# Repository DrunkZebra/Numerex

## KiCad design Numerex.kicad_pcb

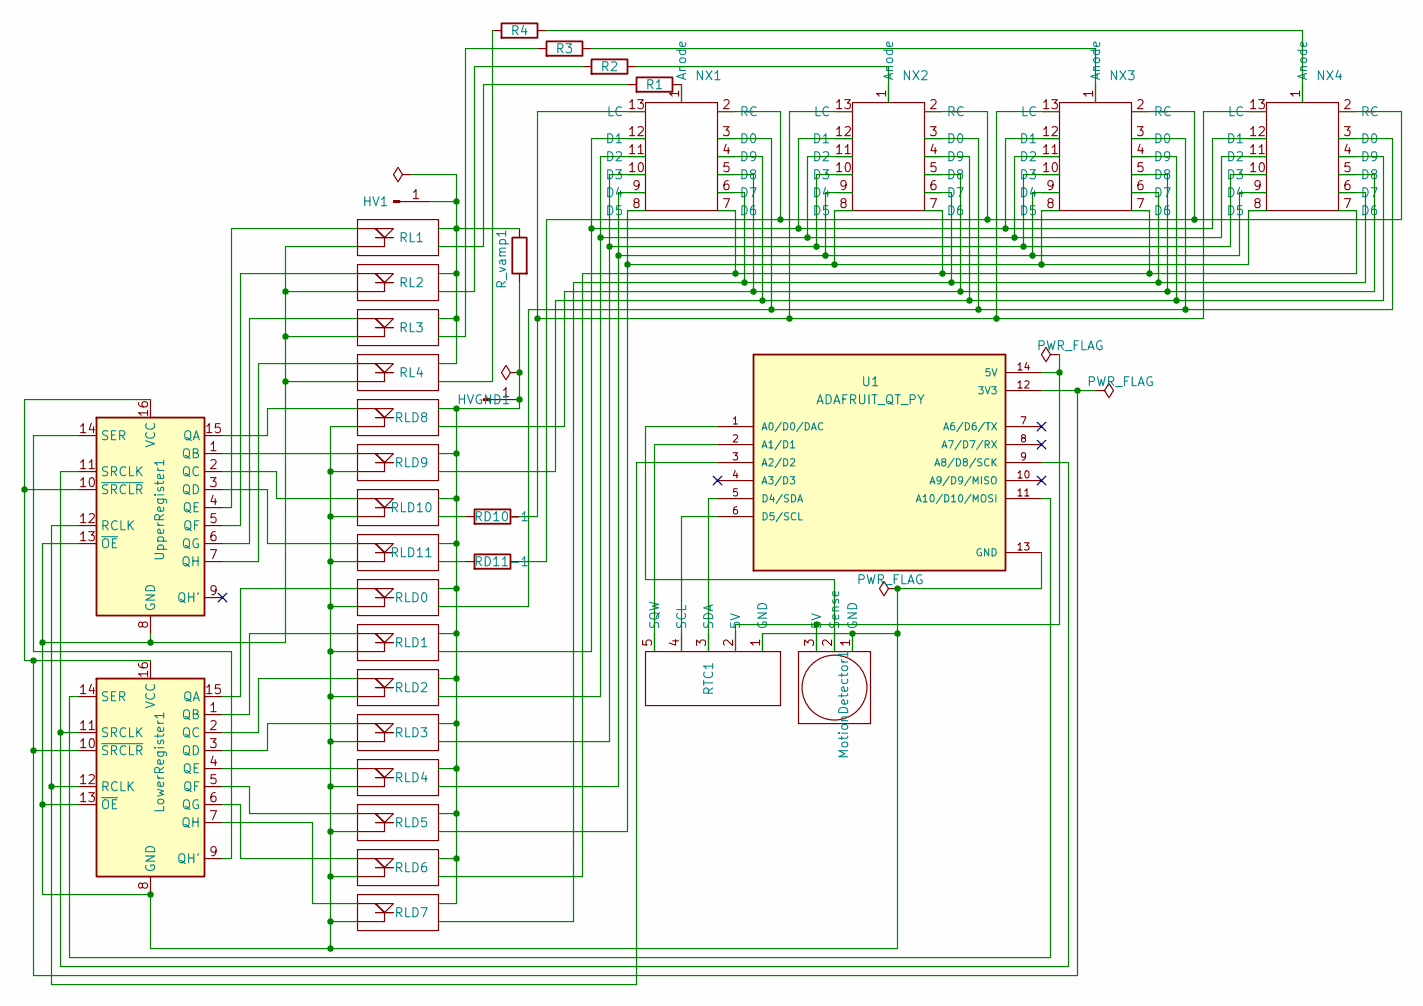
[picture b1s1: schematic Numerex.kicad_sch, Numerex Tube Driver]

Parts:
HV1: 170; PinHeader_1x01_P1.00mm_Vertical
HVGND1: PinHeader_1x01_P1.00mm_Vertical
LowerRegister1: SN74HC595DR; SOIC-16_3.9x9.9mm_P1.27mm
MotionDetector1: PinHeader_1x03_P2.54mm_Vertical
NX1, NX2, NX3, NX4: IN-14
R1, R2, R3, R4: 22k; R_1206_3216Metric_Pad1.30x1.75mm_HandSolder
RD10-1, RD11-1: 10k; R_1206_3216Metric_Pad1.30x1.75mm_HandSolder
RL1, RL2, RL3, RL4: SOP-4_3.8x4.1mm_P2.54mm
RLD0, RLD1, RLD2, RLD3, RLD4, RLD5, RLD6, RLD7, RLD8, RLD9, RLD10, RLD11: SOP-4_3.8x4.1mm_P2.54mm
RTC1: RTC
R_vamp1: 22k; R_1206_3216Metric_Pad1.30x1.75mm_HandSolder
U1: ADAFRUIT_QT_PY; MODULE_ADAFRUIT_QT_PY; PARTREV 2022-12-12
UpperRegister1: SN74HC595DR; SOIC-16_3.9x9.9mm_P1.27mm

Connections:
unnamed 0: HV1.1, RL1.4 (VL), RL2.4 (VL), RL3.4 (VL), RL4.4 (VL), R_vamp1.2; also elsewhere on the board
unnamed 1: HVGND1.1, RLD0.4 (VL), RLD1.4 (VL), RLD2.4 (VL), RLD3.4 (VL), RLD4.4 (VL), RLD5.4 (VL), RLD6.4 (VL), RLD7.4 (VL), RLD8.4 (VL), RLD9.4 (VL), RLD10.4 (VL), RLD11.4 (VL), R_vamp1.1; also elsewhere on the board
unnamed 2: LowerRegister1.8 (GND), LowerRegister1.13 (~OE), MotionDetector1.1 (GND), RL1.2 (Diode-), RL2.2 (Diode-), RL3.2 (Diode-), RL4.2 (Diode-), RLD0.2 (Diode-), RLD1.2 (Diode-), RLD2.2 (Diode-), RLD3.2 (Diode-), RLD4.2 (Diode-), RLD5.2 (Diode-), RLD6.2 (Diode-), RLD7.2 (Diode-), RLD8.2 (Diode-), RLD9.2 (Diode-), RLD10.2 (Diode-), RLD11.2 (Diode-), RTC1.1 (GND), U1.13 (GND), UpperRegister1.8 (GND), UpperRegister1.13 (~OE); also elsewhere on the board
unnamed: LowerRegister1.15 (QA), RLD0.1 (Diode+)
unnamed: LowerRegister1.1 (QB), RLD1.1 (Diode+)
unnamed: LowerRegister1.2 (QC), RLD2.1 (Diode+)
unnamed: LowerRegister1.3 (QD), RLD3.1 (Diode+)
unnamed: LowerRegister1.4 (QE), RLD4.1 (Diode+)
unnamed: LowerRegister1.5 (QF), RLD5.1 (Diode+)
unnamed: LowerRegister1.6 (QG), RLD6.1 (Diode+)
unnamed: LowerRegister1.9 (QH'), UpperRegister1.14 (SER)
unnamed: LowerRegister1.7 (QH), RLD7.1 (Diode+)
unnamed 12: LowerRegister1.12 (RCLK), U1.3 (A2/D2), UpperRegister1.12 (RCLK); also elsewhere on the board
unnamed 13: LowerRegister1.14 (SER), U1.11 (A10/D10/MOSI); also elsewhere on the board
unnamed 14: LowerRegister1.11 (SRCLK), U1.9 (A8/D8/SCK), UpperRegister1.11 (SRCLK); also elsewhere on the board
unnamed 15: LowerRegister1.10 (~SRCLR), LowerRegister1.16 (VCC), U1.12 (3V3), UpperRegister1.10 (~SRCLR), UpperRegister1.16 (VCC); also elsewhere on the board
unnamed 16: MotionDetector1.3 (5V), RTC1.2 (5V), U1.14 (5V); also elsewhere on the board
unnamed 17: MotionDetector1.2 (Sense), U1.1 (A0/D0/DAC); also elsewhere on the board
unnamed: NX1.1 (Anode), R1.2
unnamed: NX1.3 (D0), NX2.3 (D0), NX3.3 (D0), NX4.3 (D0), RLD0.3 (Load)
unnamed: NX1.12 (D1), NX2.12 (D1), NX3.12 (D1), NX4.12 (D1), RLD1.3 (Load)
unnamed: NX1.11 (D2), NX2.11 (D2), NX3.11 (D2), NX4.11 (D2), RLD2.3 (Load)
unnamed: NX1.10 (D3), NX2.10 (D3), NX3.10 (D3), NX4.10 (D3), RLD3.3 (Load)
unnamed: NX1.9 (D4), NX2.9 (D4), NX3.9 (D4), NX4.9 (D4), RLD4.3 (Load)
unnamed: NX1.8 (D5), NX2.8 (D5), NX3.8 (D5), NX4.8 (D5), RLD5.3 (Load)
unnamed: NX1.7 (D6), NX2.7 (D6), NX3.7 (D6), NX4.7 (D6), RLD6.3 (Load)
unnamed: NX1.6 (D7), NX2.6 (D7), NX3.6 (D7), NX4.6 (D7), RLD7.3 (Load)
unnamed: NX1.5 (D8), NX2.5 (D8), NX3.5 (D8), NX4.5 (D8), RLD8.3 (Load)
unnamed: NX1.4 (D9), NX2.4 (D9), NX3.4 (D9), NX4.4 (D9), RLD9.3 (Load)
unnamed: NX1.13 (LC), NX2.13 (LC), NX3.13 (LC), NX4.13 (LC), RD10-1.2
unnamed: NX1.2 (RC), NX2.2 (RC), NX3.2 (RC), NX4.2 (RC), RD11-1.2
unnamed: NX2.1 (Anode), R2.2
unnamed: NX3.1 (Anode), R3.2
unnamed: NX4.1 (Anode), R4.2
unnamed: RL1.1 (Diode+), UpperRegister1.4 (QE)
unnamed: R1.1, RL1.3 (Load)
unnamed: RL2.1 (Diode+), UpperRegister1.5 (QF)
unnamed: R2.1, RL2.3 (Load)
unnamed: RL3.1 (Diode+), UpperRegister1.6 (QG)
unnamed: R3.1, RL3.3 (Load)
unnamed: RL4.1 (Diode+), UpperRegister1.7 (QH)
unnamed: R4.1, RL4.3 (Load)
unnamed: RLD8.1 (Diode+), UpperRegister1.15 (QA)
unnamed: RLD9.1 (Diode+), UpperRegister1.1 (QB)
unnamed: RLD10.1 (Diode+), UpperRegister1.2 (QC)
unnamed: RD10-1.1, RLD10.3 (Load)
unnamed: RLD11.1 (Diode+), UpperRegister1.3 (QD)
unnamed: RD11-1.1, RLD11.3 (Load)
unnamed 48: RTC1.4 (SCL), U1.6 (D5/SCL); also elsewhere on the board
unnamed 49: RTC1.3 (SDA), U1.5 (D4/SDA); also elsewhere on the board
unnamed 50: RTC1.5 (SQW), U1.2 (A1/D1); also elsewhere on the board

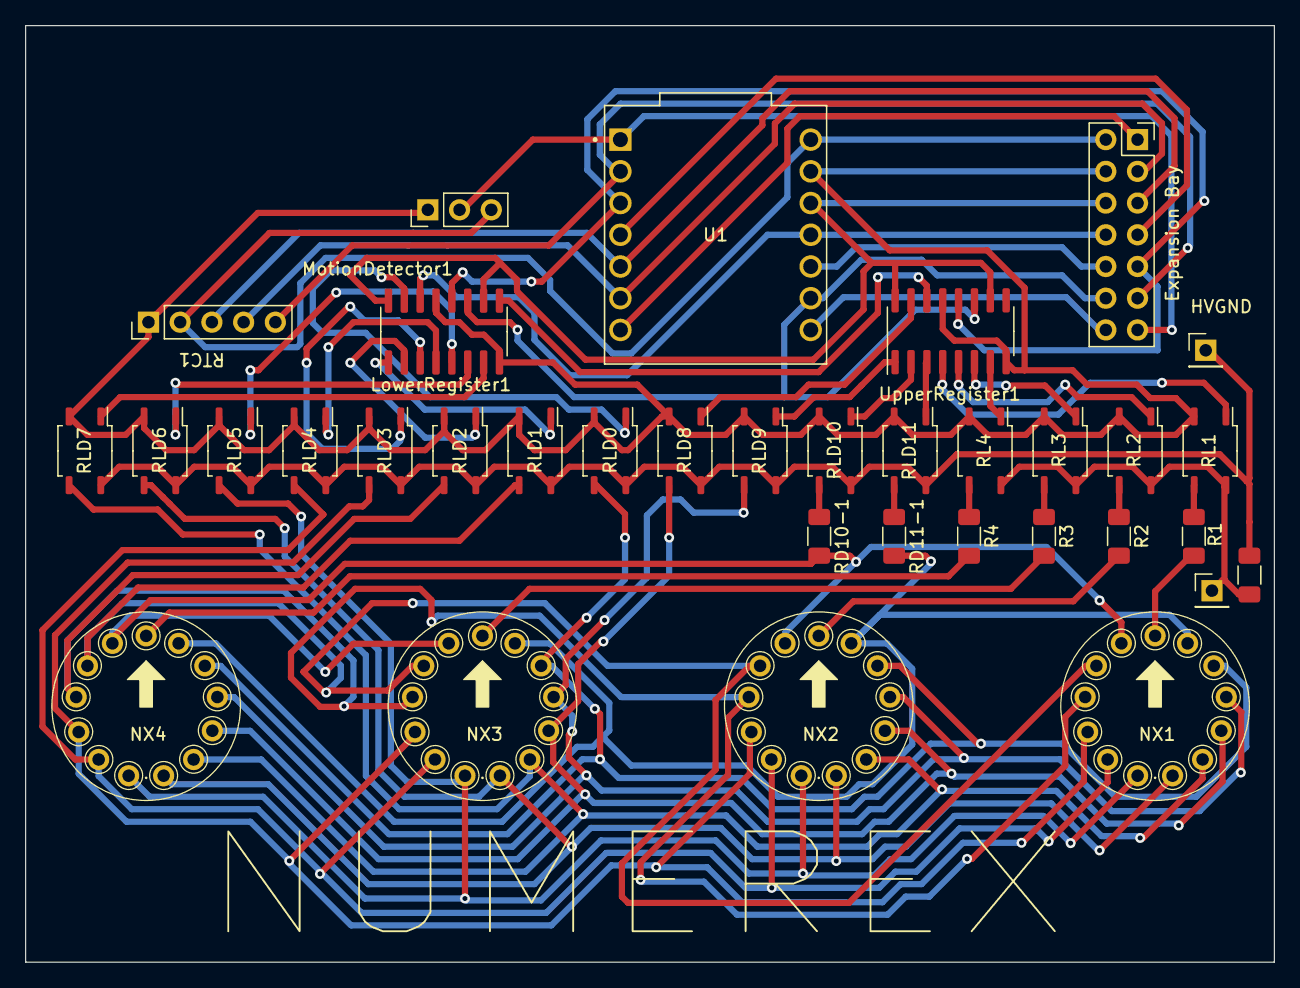
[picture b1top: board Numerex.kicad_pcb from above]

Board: 2 copper layers, 100.0 x 75.0 mm, 35 parts (0 on the bottom side), 51 nets.

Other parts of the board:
Expansion Bay: PinSocket_2x07_P2.54mm_Vertical
HV: PinHeader_1x01_P2.54mm_Vertical
HVGND: PinHeader_1x01_P2.54mm_Vertical

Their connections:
unnamed 0: HV.2; also elsewhere on the board
unnamed 1: HVGND.1; also elsewhere on the board
unnamed 2: Expansion Bay.4; also elsewhere on the board
unnamed 12: Expansion Bay.9; also elsewhere on the board
unnamed 13: Expansion Bay.8; also elsewhere on the board
unnamed 14: Expansion Bay.12; also elsewhere on the board
unnamed 15: Expansion Bay.6; also elsewhere on the board
unnamed 16: Expansion Bay.2; also elsewhere on the board
unnamed 17: Expansion Bay.13; also elsewhere on the board
unnamed 48: Expansion Bay.3; also elsewhere on the board
unnamed 49: Expansion Bay.5; also elsewhere on the board
unnamed 50: Expansion Bay.11; also elsewhere on the board

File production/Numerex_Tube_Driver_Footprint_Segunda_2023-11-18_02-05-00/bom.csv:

Designator,Footprint,Quantity,Value,LCSC Part #
"GND1, HVGND1, RCLK1, SDA1",PinHeader_1x01_P1.00mm_Vertical,4,~,
HV1,PinHeader_1x01_P1.00mm_Vertical,1,170,
"LowerRegister1, UpperRegister1",SOIC-16_3.9x9.9mm_P1.27mm,2,74HC595,
"NX1, NX2, NX3, NX4",IN-14,4,~,
"R1, R2, R3, R4, R_vamp1",1206,5,22k,
"RA1, RA2, RA3, RA4, RD0, RD1, RD10, RD11, RD2, RD3, RD4, RD5, RD6, RD7, RD8, RD9",1206,16,1500,
"RD10-1, RD11-1",1206,2,10k,
"RL1, RL2, RL3, RL4, RLD0, RLD1, RLD10, RLD11, RLD2, RLD3, RLD4, RLD5, RLD6, RLD7, RLD8, RLD9",SOP-4_3.8x4.1mm_P2.54mm,16,~,
SCLK1,PinHeader_1x01_P1.00mm_Vertical,1,SCLK,
VIN1,PinHeader_1x01_P1.00mm_Vertical,1,3.3,
